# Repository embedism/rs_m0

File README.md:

# RS M0 Necklace Dev Kit

The RS M0 Necklace Dev Kit is a tiny dev board based on the insanely powerful Atmel SAMD21 series of Arm M0 based processors.

This repo contains all of the design files so that you can understand the circuit and even remix and build upon it yourself!

## Usage

The UF2 bootloader means that you can drag-and-drop your compiled code onto the dev kit as it if was a USB memory stick.

You can create programs using [Microsoft Make Code][make code]. Use the `Adafruit Gemma M0` as the device as the RS M0 Necklace Devkit isn't available to the public just yet!

After creating your program, click on download and drag-n-drop the .uf2 file onto your RS M0 USB drive - it's as simple as that!

## Troubleshooting

If your dev kit isn't immediately recognised by your computer then you may need to install some drivers from [here][ada-drivers]. Mac, Linux, and most Windows 10 users won't need to do this. If you need more guidance then take a look at [this guide from Adafruit][ada-driver-guide].

## License and Credit

The RS M0 Necklace Dev Kit is based on the [Adafruit Gemma M0][ada-m0], licensed under Creative Commons Attribution-ShareAlike 3.0 Unported.

This project is also released under Creative Commons Attribution-ShareAlike 3.0 Unported.

The bootloader is based upon the [Microsoft UF2 Bootloader][uf2], licensed under the MIT license.

Additional resources were used from Sparkfun and other sources. For more information see `license.txt`.

We have:

- added a placeholder for a battery charger,
- added a PCB-USB connector so you can get coding without any extra cables,
- broken out the data pins for the Neopixel so you can add external LEDs easily,
- added some through-hole footprints so that you can solder on 0.1" pin header and put your dev kit into a breadboard.
- recompiled the bootloader to include the dev kit's name

This project was carried out on behalf of [RS Components Grassroots][grass-roots] by [Embedism][emb].

[//]: #
[ada-m0]: https://github.com/adafruit/Adafruit-Gemma-M0-PCB
[uf2]: https://github.com/Microsoft/uf2
[grass-roots]: https://uk.rs-online.com/web/generalDisplay.html?id=Grass-Roots
[emb]: https://embedism.com
[make code]: https://maker.makecode.com/#
[ada-drivers]: https://github.com/adafruit/Adafruit_Windows_Drivers/releases/tag/2.5.0.0
[ada-driver-guide]: https://learn.adafruit.com/adafruit-gemma-m0/windows-driver-installation

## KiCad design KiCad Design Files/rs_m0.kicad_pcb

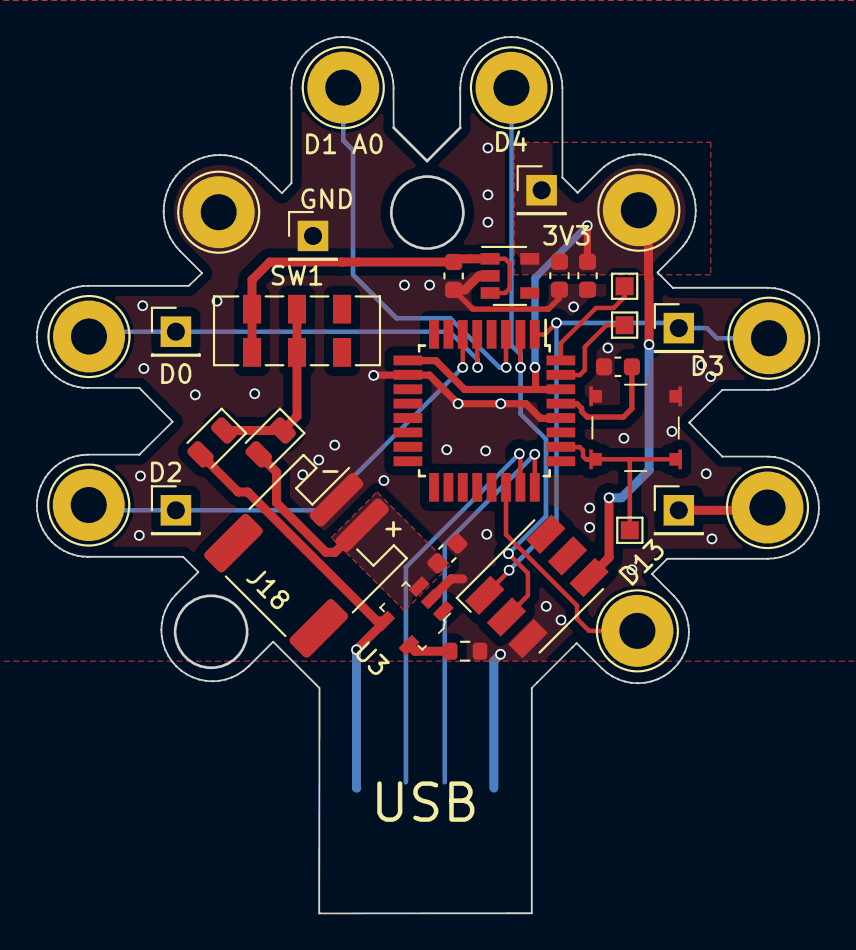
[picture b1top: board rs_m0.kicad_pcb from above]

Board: 2 copper layers, 43.4 x 48.6 mm, 34 parts (1 on the bottom side), 20 nets.

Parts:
C1, C3: 1uF; C_0603_1608Metric
C2, C4, C5: 10uF; C_0603_1608Metric
D1, D2: D_Schottky; D_0805_2012Metric
D3: APA102; LED_RGB_5050-6
J1, J2, J3, J4, J5, J7, J8, J9, J10: Conn_01x01_Female; TestPoint_THTPad_D4.0mm_Drill2.0mm
J11, J12, J13, J14, J15, J16: Conn_01x01_Female; PinHeader_1x01_P2.54mm_Vertical
J18: JST_2MM_MALE; JST_PH_S2B-PH-SM4-TB_1x02-1MP_P2.00mm_Horizontal
R1: 10k; R_0603_1608Metric
S1: TL3315NF160Q; Switch_Tactile_SMD_4.5x4.5mm_TL3315NF160Q
SW1: SW_Push_DPDT; SW_DPDT_CK_JS202011JCQN
TP1, TP2, TP3: TestPoint; TestPoint_Pad_1.0x1.0mm
U1: ATSAMD21E18A-A; TQFP-32_7x7mm_P0.8mm
U2: AP2112K-3.3; SOT-23-5
U3: MCP73831T-2ACI_OT; SOT-753
USB: USB_A; usb

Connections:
+3V3: C3.2, C4.2, D3.4, J2.1, J15.1, U1.9, U1.30, U2.5
+BATT: C5.2, D1.2, J18.2, U3.3
/D0_SDA_TX: J8.1, J14.1, U1.5
/D1_A0: J10.1, U1.3
/D2_SCL_RX: J7.1, J13.1, U1.6
/D3: D3.1, J3.1, J11.1, U1.1
/D4: D3.2, J1.1, U1.2
/D13: J5.1, U1.22
/USB_DM: U1.23, USB.2
/USB_DP: U1.24, USB.3
GND: C1.2, C2.1, C3.1, C4.1, C5.1, D3.3, J9.1, J16.1, J18.1, R1.2, S1.1, S1.2, U1.10, U1.28, U2.2, U3.2, USB.4
unnamed: C1.1, U1.29
unnamed: C2.2, SW1.1, SW1.4, U2.1, U2.3
unnamed: D1.1, D2.1, SW1.2, SW1.5
unnamed: J4.1, J12.1
unnamed: R1.1, U3.5
unnamed: S1.3, S1.4, TP1.1, U1.26
unnamed: TP2.1, U1.31
unnamed: TP3.1, U1.32
VBUS: D2.2, U3.4, USB.1

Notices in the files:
README.md:
License: CC BY-SA 3.0
